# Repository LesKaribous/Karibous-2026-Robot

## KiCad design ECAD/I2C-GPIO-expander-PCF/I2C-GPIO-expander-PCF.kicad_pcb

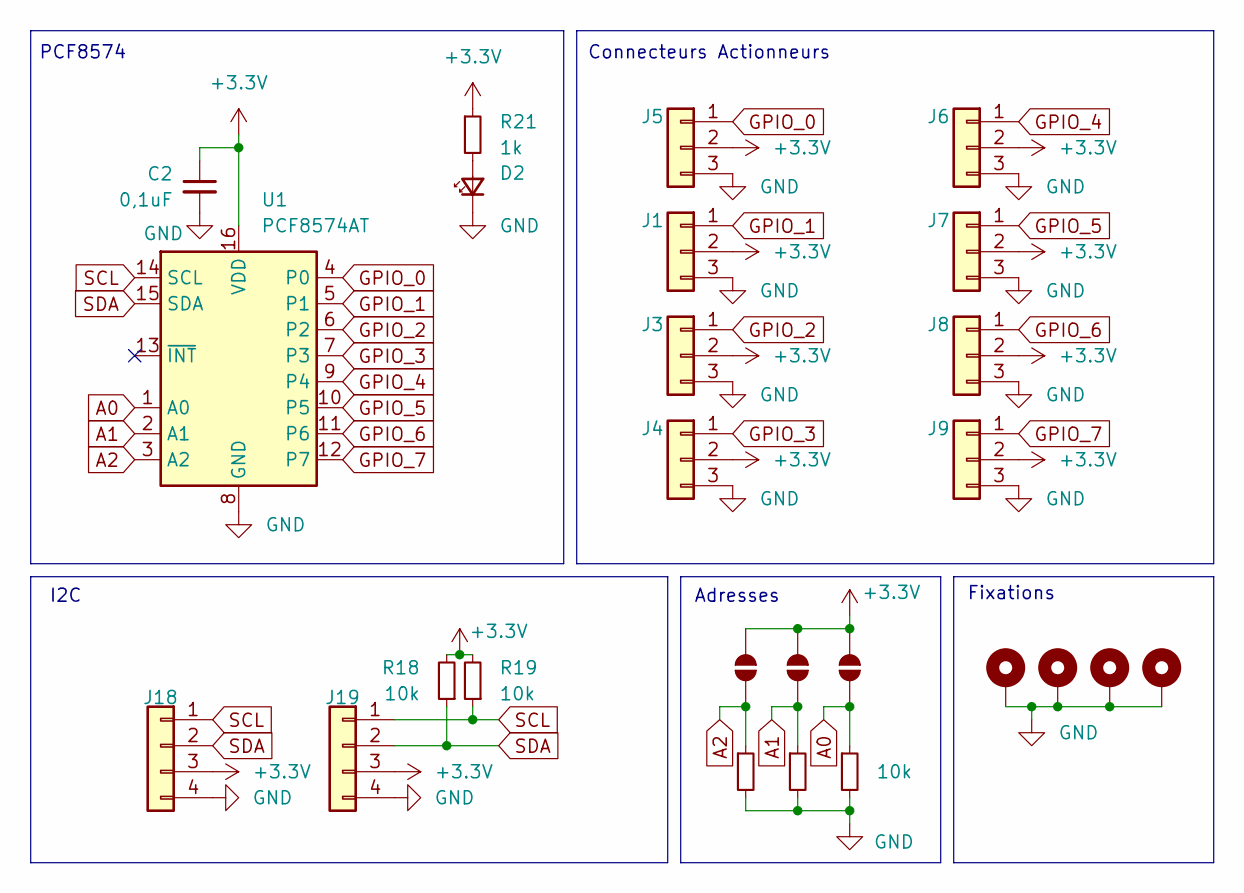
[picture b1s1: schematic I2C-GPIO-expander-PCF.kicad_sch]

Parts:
C2: 0,1uF; C_1206_3216Metric_Pad1.33x1.80mm_HandSolder
D2: LED_Small; LED_1206_3216Metric_Pad1.42x1.75mm_HandSolder
H1, H2, H3, H4: MountingHole_Pad; MountingHole_3.2mm_M3_Pad_Via
J1, J3, J4, J5, J6, J7, J8, J9: Conn_01x03; PinHeader_1x03_P2.54mm_Vertical
J18, J19: Conn_01x04; Molex_KK-254_AE-6410-04A_1x04_P2.54mm_Vertical
JP1, JP2, JP3: SolderJumper_2_Open; SolderJumper-2_P1.3mm_Open_RoundedPad1.0x1.5mm
R18, R19, R22, R23, R24: 10k; R_1206_3216Metric_Pad1.30x1.75mm_HandSolder
R21: 1k; R_1206_3216Metric_Pad1.30x1.75mm_HandSolder
U1: PCF8574AT; SOIC-16W_7.5x10.3mm_P1.27mm

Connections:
+3.3V: C2.1, J1.2, J3.2, J4.2, J5.2, J6.2, J7.2, J8.2, J9.2, J18.3, J19.3, JP1.2 (B), JP2.2 (B), JP3.2 (B), R18.2, R19.2, R21.1, U1.16 (VDD)
A0: JP1.1 (A), R22.1, U1.1 (A0)
A1: JP2.1 (A), R23.1, U1.2 (A1)
A2: JP3.1 (A), R24.1, U1.3 (A2)
GND: C2.2, D2.1 (K), H1.1, H2.1, H3.1, H4.1, J1.3, J3.3, J4.3, J5.3, J6.3, J7.3, J8.3, J9.3, J18.4, J19.4, R22.2, R23.2, R24.2, U1.8 (GND)
GPIO_0: J5.1, U1.4 (P0)
GPIO_1: J1.1, U1.5 (P1)
GPIO_2: J3.1, U1.6 (P2)
GPIO_3: J4.1, U1.7 (P3)
GPIO_4: J6.1, U1.9 (P4)
GPIO_5: J7.1, U1.10 (P5)
GPIO_6: J8.1, U1.11 (P6)
GPIO_7: J9.1, U1.12 (P7)
unnamed: D2.2 (A), R21.2
SCL: J18.1, J19.1, R19.1, U1.14 (SCL)
SDA: J18.2, J19.2, R18.1, U1.15 (SDA)

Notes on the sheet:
Adresses
Fixations
PCF8574
I2C
Connecteurs Actionneurs

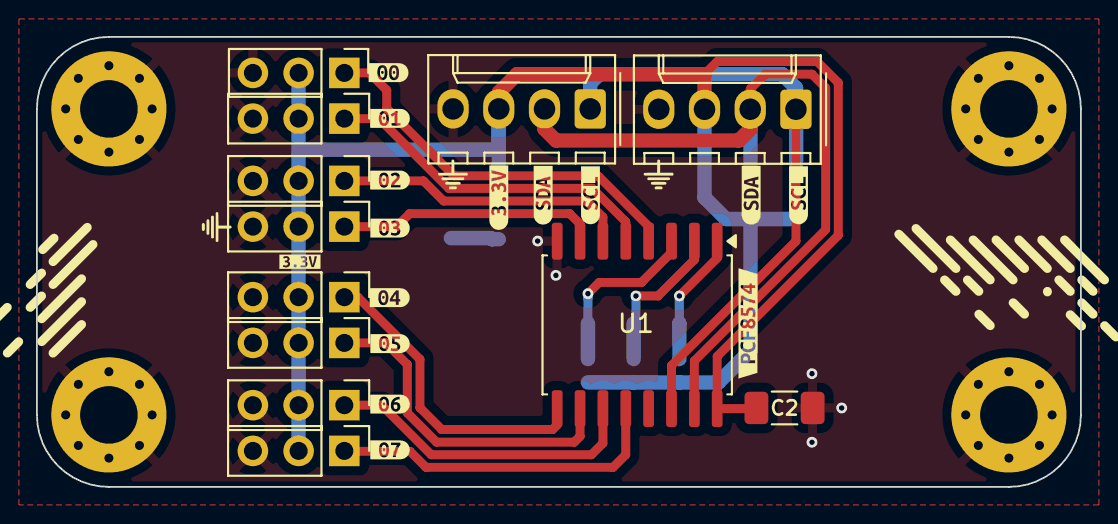
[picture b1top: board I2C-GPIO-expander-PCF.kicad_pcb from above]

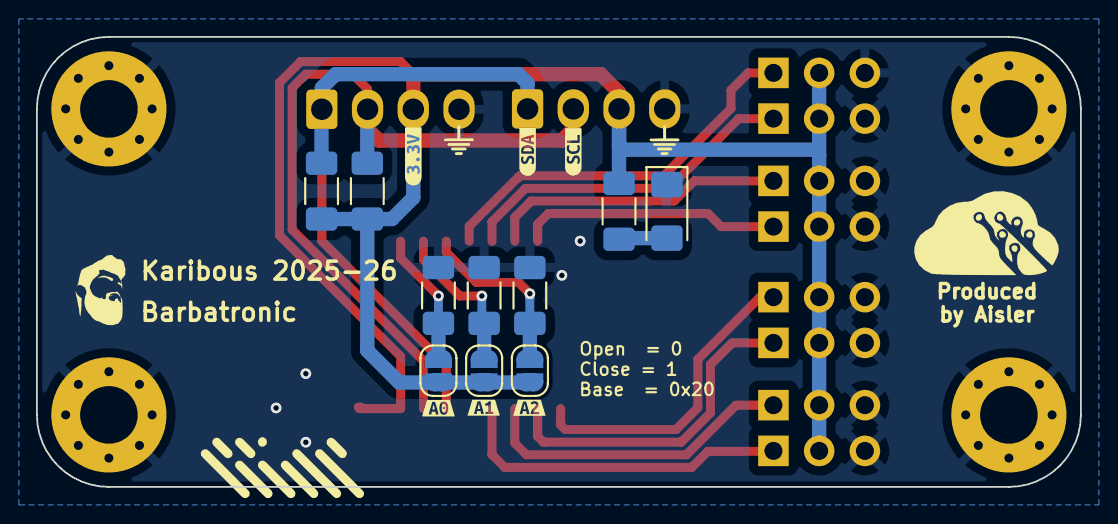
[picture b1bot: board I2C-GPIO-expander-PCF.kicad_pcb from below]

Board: 2 copper layers, 58.0 x 25.0 mm, 47 parts (16 on the bottom side), 16 nets.

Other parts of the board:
kibuzzard-698C52C9: G***; kibuzzard-698C52C9
kibuzzard-698C52CF: G***; kibuzzard-698C52CF
kibuzzard-698C52D4: G***; kibuzzard-698C52D4
kibuzzard-698C52DA: G***; kibuzzard-698C52DA
kibuzzard-698C52E2: G***; kibuzzard-698C52E2
kibuzzard-698C52E7: G***; kibuzzard-698C52E7
kibuzzard-698C52ED: G***; kibuzzard-698C52ED
kibuzzard-698C52F2: G***; kibuzzard-698C52F2
kibuzzard-698C538A: G***; kibuzzard-698C538A
kibuzzard-698C5220: G***; kibuzzard-698C5220
kibuzzard-67954CC0: G***; kibuzzard-67954CC0
kibuzzard-67954D1A, kibuzzard-67954D1A#2: G***; kibuzzard-67954D1A
kibuzzard-67954D30, kibuzzard-67954D30#2: G***; kibuzzard-67954D30
kibuzzard-67954E00: G***; kibuzzard-67954E00
kibuzzard-67954E2A: G***; kibuzzard-67954E2A
kibuzzard-67954E2F: G***; kibuzzard-67954E2F
kibuzzard-67954E7A: G***; kibuzzard-67954E7A
kibuzzard-67954E99: G***; kibuzzard-67954E99
kibuzzard-67954EA0: G***; kibuzzard-67954EA0

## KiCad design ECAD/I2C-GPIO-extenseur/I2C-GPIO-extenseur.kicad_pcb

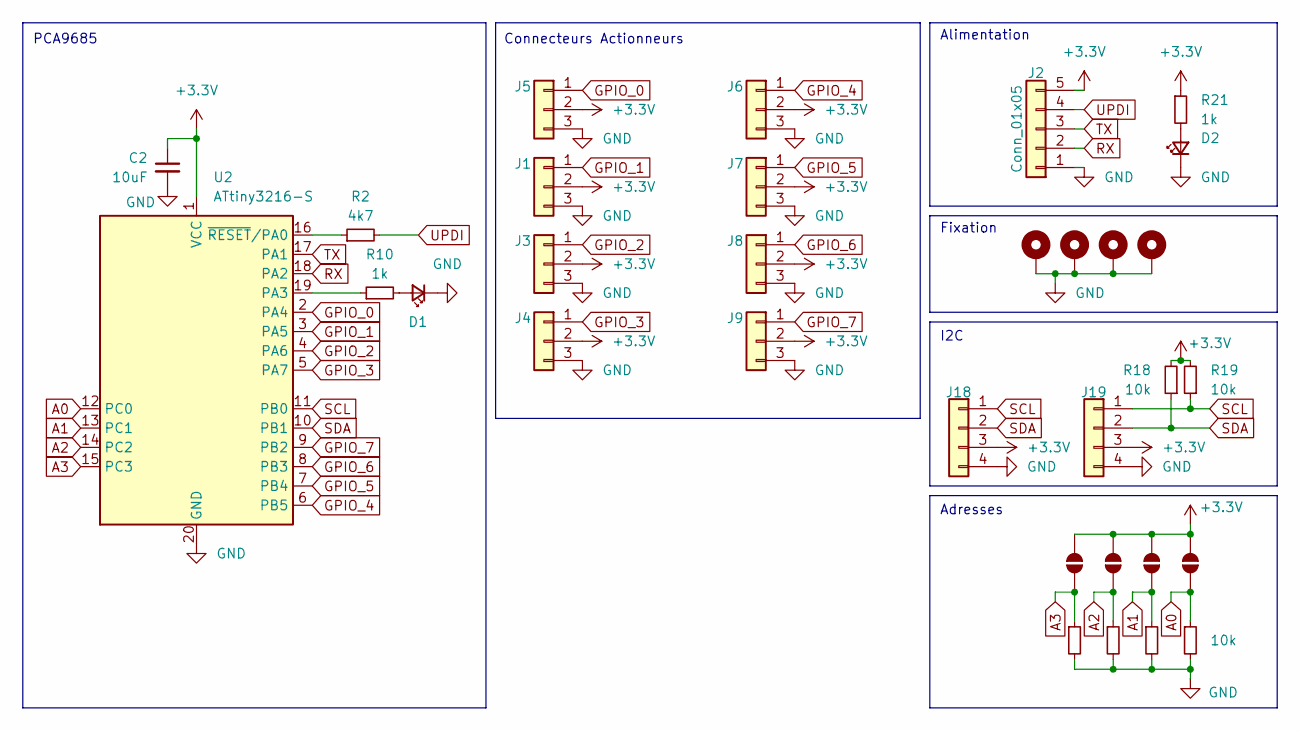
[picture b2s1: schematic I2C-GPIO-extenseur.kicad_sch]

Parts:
C2: 10uF; C_1206_3216Metric_Pad1.33x1.80mm_HandSolder
D1, D2: LED_Small; LED_1206_3216Metric_Pad1.42x1.75mm_HandSolder
H1, H2, H3, H4: MountingHole_Pad; MountingHole_3.2mm_M3_Pad_Via
J1, J3, J4, J5, J6, J7, J8, J9: Conn_01x03; PinHeader_1x03_P2.54mm_Vertical
J2: Conn_01x05; PinHeader_1x05_P2.54mm_Vertical
J18, J19: Conn_01x04; Molex_KK-254_AE-6410-04A_1x04_P2.54mm_Vertical
JP1, JP2, JP3, JP4: SolderJumper_2_Open; SolderJumper-2_P1.3mm_Open_RoundedPad1.0x1.5mm
R1, R18, R19, R22, R23, R24: 10k; R_1206_3216Metric_Pad1.30x1.75mm_HandSolder
R2: 4k7; R_1206_3216Metric_Pad1.30x1.75mm_HandSolder
R10, R21: 1k; R_1206_3216Metric_Pad1.30x1.75mm_HandSolder
U2: ATtiny3216-S; SOIC-20W_7.5x12.8mm_P1.27mm

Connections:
+3.3V: C2.1, J1.2, J2.5, J3.2, J4.2, J5.2, J6.2, J7.2, J8.2, J9.2, J18.3, J19.3, JP1.2 (B), JP2.2 (B), JP3.2 (B), JP4.2 (B), R18.2, R19.2, R21.1, U2.1 (VCC)
A0: JP1.1 (A), R22.1, U2.12 (PC0)
A1: JP2.1 (A), R23.1, U2.13 (PC1)
A2: JP3.1 (A), R24.1, U2.14 (PC2)
A3: JP4.1 (A), R1.1, U2.15 (PC3)
GND: C2.2, D1.1 (K), D2.1 (K), H1.1, H2.1, H3.1, H4.1, J1.3, J2.1, J3.3, J4.3, J5.3, J6.3, J7.3, J8.3, J9.3, J18.4, J19.4, R1.2, R22.2, R23.2, R24.2, U2.20 (GND)
GPIO_0: J5.1, U2.2 (PA4)
GPIO_1: J1.1, U2.3 (PA5)
GPIO_2: J3.1, U2.4 (PA6)
GPIO_3: J4.1, U2.5 (PA7)
GPIO_4: J6.1, U2.6 (PB5)
GPIO_5: J7.1, U2.7 (PB4)
GPIO_6: J8.1, U2.8 (PB3)
GPIO_7: J9.1, U2.9 (PB2)
unnamed: D1.2 (A), R10.2
unnamed: D2.2 (A), R21.2
unnamed: R10.1, U2.19 (PA3)
unnamed: R2.1, U2.16 (~RESET/PA0)
RX: J2.2, U2.18 (PA2)
SCL: J18.1, J19.1, R19.1, U2.11 (PB0)
SDA: J18.2, J19.2, R18.1, U2.10 (PB1)
TX: J2.3, U2.17 (PA1)
UPDI: J2.4, R2.2

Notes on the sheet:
Adresses
Alimentation
Fixation
PCA9685
I2C
Connecteurs Actionneurs

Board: 2 copper layers, 53 parts (24 on the bottom side), 23 nets, no tracks yet.

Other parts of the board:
kibuzzard-67954B90: G***; kibuzzard-67954B90
kibuzzard-67954C4A: G***; kibuzzard-67954C4A
kibuzzard-67954C5E: G***; kibuzzard-67954C5E
kibuzzard-67954C44: G***; kibuzzard-67954C44
kibuzzard-67954C57: G***; kibuzzard-67954C57
kibuzzard-67954C66: G***; kibuzzard-67954C66
kibuzzard-67954CC0: G***; kibuzzard-67954CC0
kibuzzard-67954D1A: G***; kibuzzard-67954D1A
kibuzzard-67954D30: G***; kibuzzard-67954D30
kibuzzard-67954E00: G***; kibuzzard-67954E00
kibuzzard-67954E2A: G***; kibuzzard-67954E2A
kibuzzard-67954E2F: G***; kibuzzard-67954E2F
kibuzzard-67954E3F: G***; kibuzzard-67954E3F
kibuzzard-67954E7A, kibuzzard-67954E7A#2: G***; kibuzzard-67954E7A
kibuzzard-67954E34: G***; kibuzzard-67954E34
kibuzzard-67954E39: G***; kibuzzard-67954E39
kibuzzard-67954E99, kibuzzard-67954E99#2: G***; kibuzzard-67954E99
kibuzzard-67954EA0, kibuzzard-67954EA0#2: G***; kibuzzard-67954EA0

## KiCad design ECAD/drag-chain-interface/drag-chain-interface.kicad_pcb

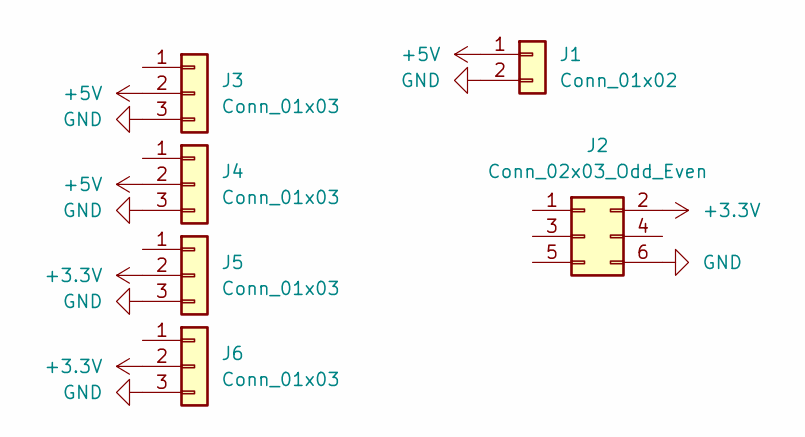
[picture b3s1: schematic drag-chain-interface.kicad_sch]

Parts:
J1: Conn_01x02; Molex_KK-396_A-41792-0002_1x02_P3.96mm_Horizontal
J2: Conn_02x03_Odd_Even; IDC-Header_2x03_P2.54mm_Vertical
J3, J4, J5, J6: Conn_01x03; PinHeader_1x03_P2.54mm_Vertical

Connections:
+3.3V: J2.2, J5.2, J6.2
+5V: J1.1, J3.2, J4.2
GND: J1.2, J2.6, J3.3, J4.3, J5.3, J6.3

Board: 2 copper layers, 6 parts (0 on the bottom side), 3 nets, no tracks yet.

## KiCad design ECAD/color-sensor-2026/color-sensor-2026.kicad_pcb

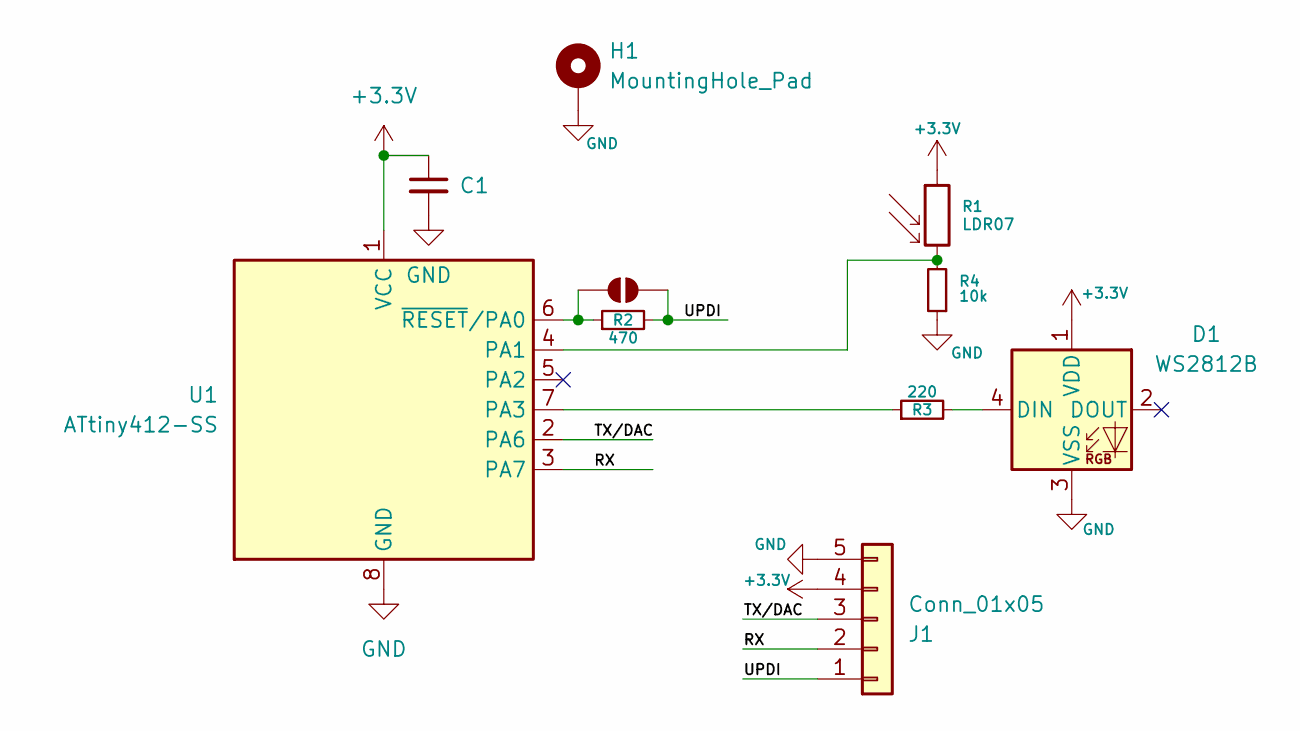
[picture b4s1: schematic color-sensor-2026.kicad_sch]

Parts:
C1: C_Small; C_1206_3216Metric_Pad1.33x1.80mm_HandSolder
D1: WS2812B; LED_WS2812B_PLCC4_5.0x5.0mm_P3.2mm
H1: MountingHole_Pad; MountingHole_3.2mm_M3_Pad_Via
J1: Conn_01x05; PinHeader_1x05_P2.54mm_Horizontal
JP2: SolderJumper_2_Open; SolderJumper-2_P1.3mm_Open_Pad1.0x1.5mm
R1: LDR07; R_LDR_5.1x4.3mm_P3.4mm_Vertical
R2: 470; R_1206_3216Metric_Pad1.30x1.75mm_HandSolder
R3: 220; R_1206_3216Metric_Pad1.30x1.75mm_HandSolder
R4: 10k; R_1206_3216Metric_Pad1.30x1.75mm_HandSolder
U1: ATtiny412-SS; SOIC-8_3.9x4.9mm_P1.27mm

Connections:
+3.3V: C1.1, D1.1 (VDD), J1.4, R1.1, U1.1 (VCC)
/RX: J1.2, U1.3 (PA7)
/TX/DAC: J1.3, U1.2 (PA6)
/UPDI: J1.1, JP2.2 (B), R2.2
GND: C1.2, D1.3 (VSS), H1.1, J1.5, R4.1, U1.8 (GND)
unnamed: D1.4 (DIN), R3.2
unnamed: JP2.1 (A), R2.1, U1.6 (~RESET/PA0)
unnamed: R1.2, R4.2, U1.4 (PA1)
unnamed: R3.1, U1.7 (PA3)

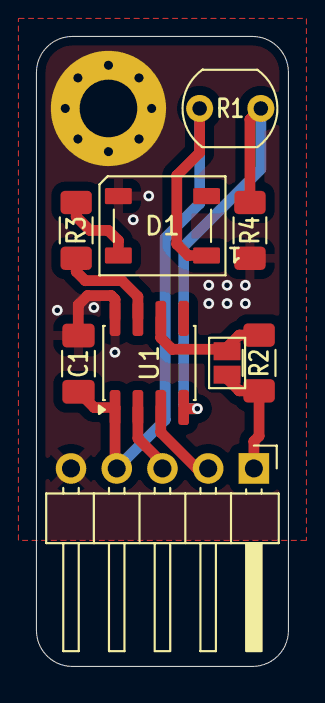
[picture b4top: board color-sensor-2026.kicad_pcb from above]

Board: 2 copper layers, 14.0 x 35.0 mm, 10 parts (0 on the bottom side), 9 nets.

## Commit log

2025-09-06 Fresh restart 2026
2025-09-07 gripper test
2025-10-12 new flat design gripper
2025-10-19 test live 240
2025-10-19 New gripper version for FreeCAD 1.1
2025-10-19 assembly gripper with WB 1.1
2025-10-27 new lifter for gripper
2025-11-02 WIP - Lifter with bearing
2025-11-02 New macro VarSetGui
2025-11-02 WIP integrate macro VarSetsGui
2025-11-02 Proto pivot V2
2025-11-03 update assembly - Two files version
2026-01-01 New color sensor
2026-01-01 V1 color sensor
2026-01-01 Clean repo - Add parrallel bar on actuator - Create 2026 base
    Moved various actuator, mechanical, electronical, and step-imported files into a new 'archives-2025' directory for better organization. Added new versions of gripper, holonomic-base, and robot files,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
2026-01-02 oskour...
2026-01-03 New assembly of the lifter - New actuator support
2026-01-04 update color sensor and gripper link
2026-01-10 new suction cup actuators
2026-01-11 add drag chain
2026-01-17 firmware - serial version
2026-01-17 3d CAd integration
2026-01-17 add yellow detection
2026-02-01 add color sensor on arms
2026-02-01 update live 252
2026-02-01 update color sensor position
2026-02-03 Attiny3216
2026-02-08 new mini extension PCB
2026-02-08 modular drag chain
2026-02-08 change diameter of the drag chain
2026-02-08 add air connector
2026-02-10 update size and position
2026-02-10 first version - PCF
2026-02-11 Silkscreen
2026-03-04 semelle pour TwinActuator
2026-04-08 Drawing for Laser and WaterJet
2026-04-11 new base gripper
2026-04-27 add VRML
2026-05-11 moult modif
